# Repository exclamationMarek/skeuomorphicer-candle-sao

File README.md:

# Skeuomorphicer candle

A more skeuomorphic, electronic candle, that you turn on using a flame and turn off by blowing on it. This is a SAO version of my standalone skeuomorphicer candle.
* It's like a real candle!
* Uses like 5 components
* No MCUs, no op-amps, literarily just one transistor
* The (simplified) schematic looks like a candle

# Simplified schematic and principle of operation

* Heat from flame causes NTC resistance to drop
* This increases the voltage on the gate of the N-MOS, so it should start conducting
* The tungsten bulb now shines, and also produces heat
* The produced heat warms the NTC. The flame can now be removed, and the candle will stay on.
* Blowing on the device temporarily cools the bulb and the NTC
* This disrupts the cycle and causes the candle to shut down

# Actual device
In addition to what is on the simplified schematic, the actual SAO PCB contains:
* A 4.7R resistor to limit the current to the bulb. This is to make it a bit dimmer and warmer, imitating a candle flame more better
* A 130R supplementary heating resistor. To ensure a better thermal latch-on, and make the device more sensitive to being blown out, a resistor placed close to the NTC is providing additional heat. Otherwise the thermal mass of the glass bulb, and the unreliable thermal coupling between it and the NTC makes the candle unreliable.
* Footprints for an LED and resistor, should one want a more power efficient version or a custom, unorthodox colour of light.

# Assembly from kit
If you received a kit at Hackaday Europe 2026, it should contain:

1x PCB
1x tiny tungsten bulb (3V nominal)
1x N-MOSFET 2302V in SOT-23
1x 100k NTC thermistor in 0603 (no marking)
1x 4.7R resistor (marked "4R7")
1x 100R resistor (marked "101")
1x  27k resistor (marked "273")
1x SAO connector

I might have accidentally removed the solder mask on the "wick" part of the candle. It makes soldering the NTC and supplementary heating resistor very hard, as it is very easy to short them to the large 3v3 plane. Sorry! Solder them first, so that you can use a multimeter to test for shorts without other parts interfering.

You can optionally place an LED in the back (or on the top of) the wick, and its current limiting resistor next to the 4.7R one.

# Operational requirements:
* Ambient temperature 22.9-23.1 degrees
* Vin: 3.25-3.35V
* Windspeed: 0-0.5m/s
* Outside of these parameters, the candle will probably turn itself on or off unprompted

First premiered at Hackaday Europe 2026 in Lecco

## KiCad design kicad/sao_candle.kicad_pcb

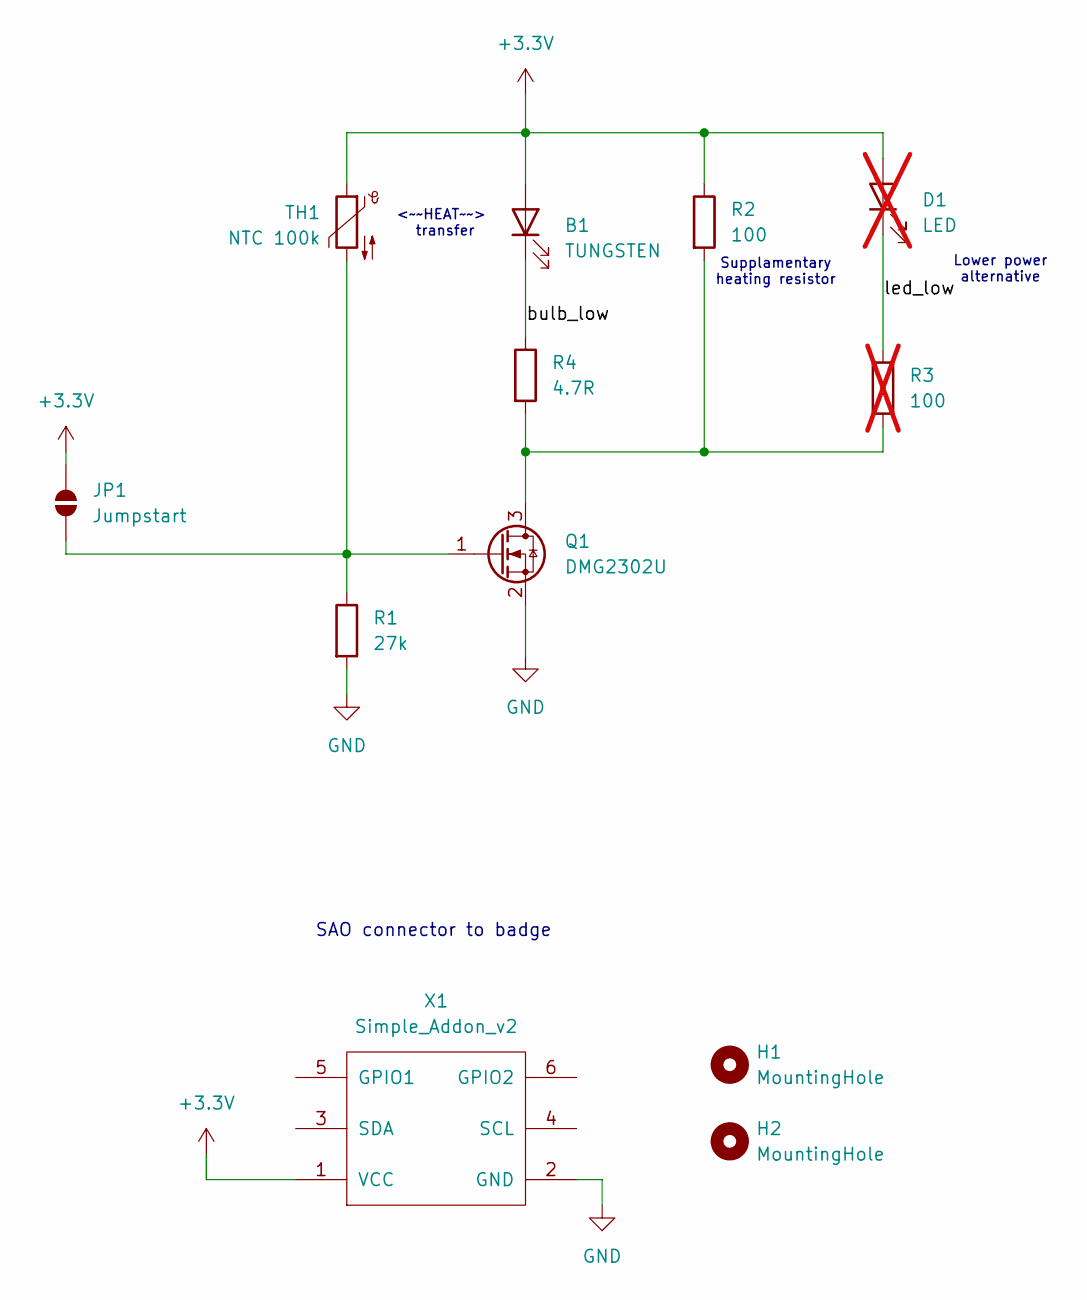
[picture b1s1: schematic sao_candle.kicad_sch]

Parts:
B1: TUNGSTEN; LED_Rectangular_W3.9mm_H1.9mm
D1: LED; R_0603_1608Metric; not fitted
H1, H2: MountingHole; MountingHole_2.2mm_M2
JP1: Jumpstart; SolderJumper-2_P1.3mm_Open_RoundedPad1.0x1.5mm
Q1: DMG2302U; SOT-23_Handsoldering
R1: 27k; R_0603_1608Metric_Pad0.98x0.95mm_HandSolder
R2: 100; R_0603_1608Metric
R3: 100; R_0603_1608Metric_Pad0.98x0.95mm_HandSolder; not fitted
R4: 4.7R; R_0603_1608Metric_Pad0.98x0.95mm_HandSolder
TH1: NTC 100k; R_0603_1608Metric
X1: Simple_Addon_v2; Simple_Addon_v2-SAO-2x3

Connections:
+3.3V: B1.2 (A), D1.2 (A), JP1.2 (B), R2.1, TH1.1, X1.1 (VCC)
/bulb_low: B1.1 (K), R4.1
/led_low: D1.1 (K), R3.1
GND: Q1.2 (S), R1.2, X1.2 (GND)
unnamed: JP1.1 (A), Q1.1 (G), R1.1, TH1.2
unnamed: Q1.3 (D), R2.2, R3.2, R4.2

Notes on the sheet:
Supplamentary heating resistor
<~~HEAT~~> transfer
Lower power alternative
SAO connector to badge

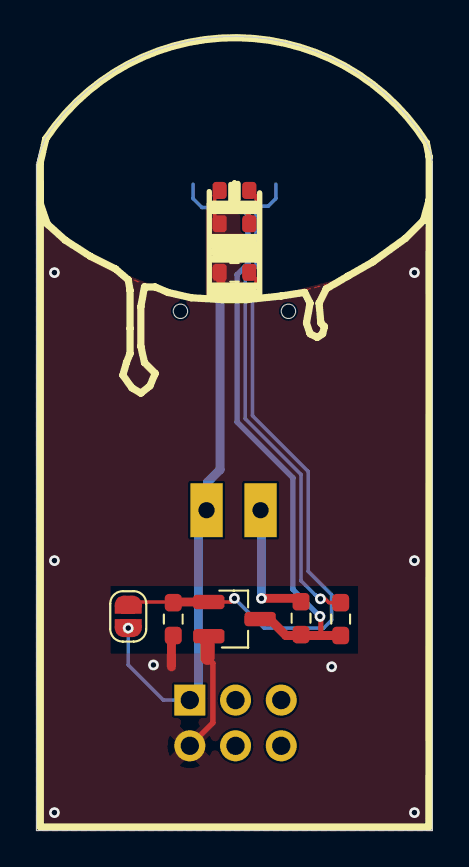
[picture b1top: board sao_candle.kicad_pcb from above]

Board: 2 copper layers, 22.0 x 44.1 mm, 12 parts (0 on the bottom side), 6 nets.

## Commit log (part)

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2026-05-14 Candle
2026-05-16 documentation
2026-05-16 fixed documentation for read this time
